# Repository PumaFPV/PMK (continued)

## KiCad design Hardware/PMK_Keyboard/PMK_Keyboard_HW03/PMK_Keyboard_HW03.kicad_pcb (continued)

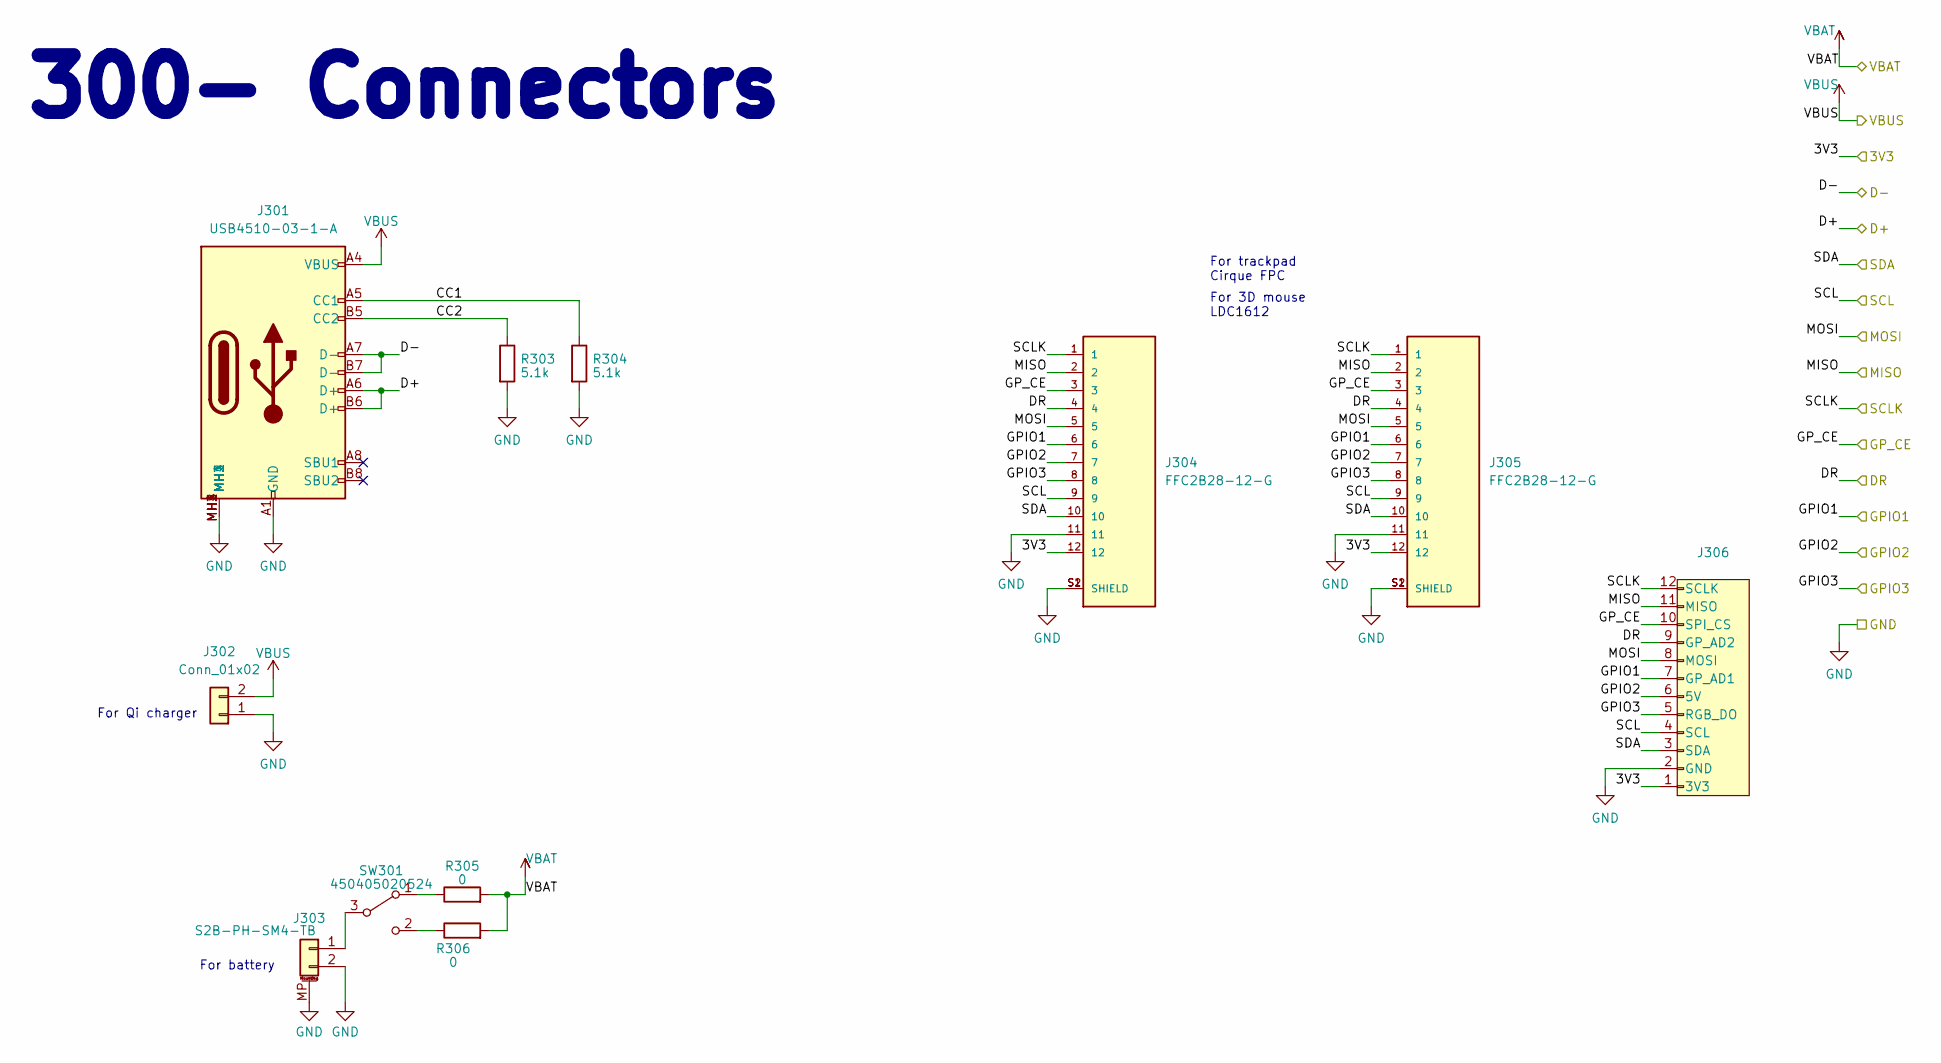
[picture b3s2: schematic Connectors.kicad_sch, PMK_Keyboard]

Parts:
J301: USB4510-03-1-A; USB4510031A; Mouser Part Number 640-USB4510031A
J302: Conn_01x02; PinHeader_1x02_P2.54mm_Vertical
J303: S2B-PH-SM4-TB; JST_PH_S2B-PH-SM4-TB_1x02-1MP_P2.00mm_Horizontal_DUALSIDE
J304, J305: FFC2B28-12-G; GCT_FFC2B28-12-G; PARTREV A; DigiKey_Part_Number 2073-FFC2B28-12-GTR-ND
J306: vik-keyboard-connector-horizontal
R303, R304: 5.1k; R_0402_1005Metric
R305, R306: 0; R_0402_1005Metric
SW301: 450405020524; 450405020524_DUALSIDE

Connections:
+3V3: J304.12, J305.12, J306.1 (3V3); also elsewhere on the board
/200- PSoM/D+: J301.A6 (D+), J301.B6 (D+); also elsewhere on the board
/200- PSoM/D-: J301.A7 (D-), J301.B7 (D-); also elsewhere on the board
/200- PSoM/DR: J304.4, J305.4, J306.9 (GP_AD2); also elsewhere on the board
/200- PSoM/GPIO1: J304.6, J305.6, J306.7 (GP_AD1); also elsewhere on the board
/200- PSoM/GPIO2: J304.7, J305.7, J306.6 (5V); also elsewhere on the board
/200- PSoM/GPIO3: J304.8, J305.8, J306.5 (RGB_DO); also elsewhere on the board
/200- PSoM/GP_CE: J304.3, J305.3, J306.10 (SPI_CS); also elsewhere on the board
/200- PSoM/SCL: J304.9, J305.9, J306.4 (SCL); also elsewhere on the board
/200- PSoM/SDA: J304.10, J305.10, J306.3 (SDA); also elsewhere on the board
/200- PSoM/SPI_CLK: J304.1, J305.1, J306.12 (SCLK); also elsewhere on the board
/200- PSoM/SPI_MISO: J304.2, J305.2, J306.11 (MISO); also elsewhere on the board
/200- PSoM/SPI_MOSI: J304.5, J305.5, J306.8 (MOSI); also elsewhere on the board
/300- Connectors/CC1: J301.A5 (CC1), R304.1
/300- Connectors/CC2: J301.B5 (CC2), R303.1
/VBAT: R305.2, R306.2; also elsewhere on the board
GND: J301.A1 (GND), J301.A12 (GND), J301.B1 (GND), J301.B12 (GND), J301.MH1, J301.MH2, J301.MH3, J301.MH4, J302.1, J303.2, J303.MP (MountPin), J304.11, J304.S1 (SHIELD), J304.S2 (SHIELD), J305.11, J305.S1 (SHIELD), J305.S2 (SHIELD), J306.2 (GND), R303.2, R304.2; also elsewhere on the board
unnamed: J303.1, SW301.3 (B)
unnamed: R305.1, SW301.1 (A)
unnamed: R306.1, SW301.2 (C)
VBUS: J301.A4 (VBUS), J301.A9 (VBUS), J301.B4 (VBUS), J301.B9 (VBUS), J302.2; also elsewhere on the board

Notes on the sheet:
300- Connectors
For battery
For trackpad Cirque FPC
For Qi charger
For 3D mouse LDC1612

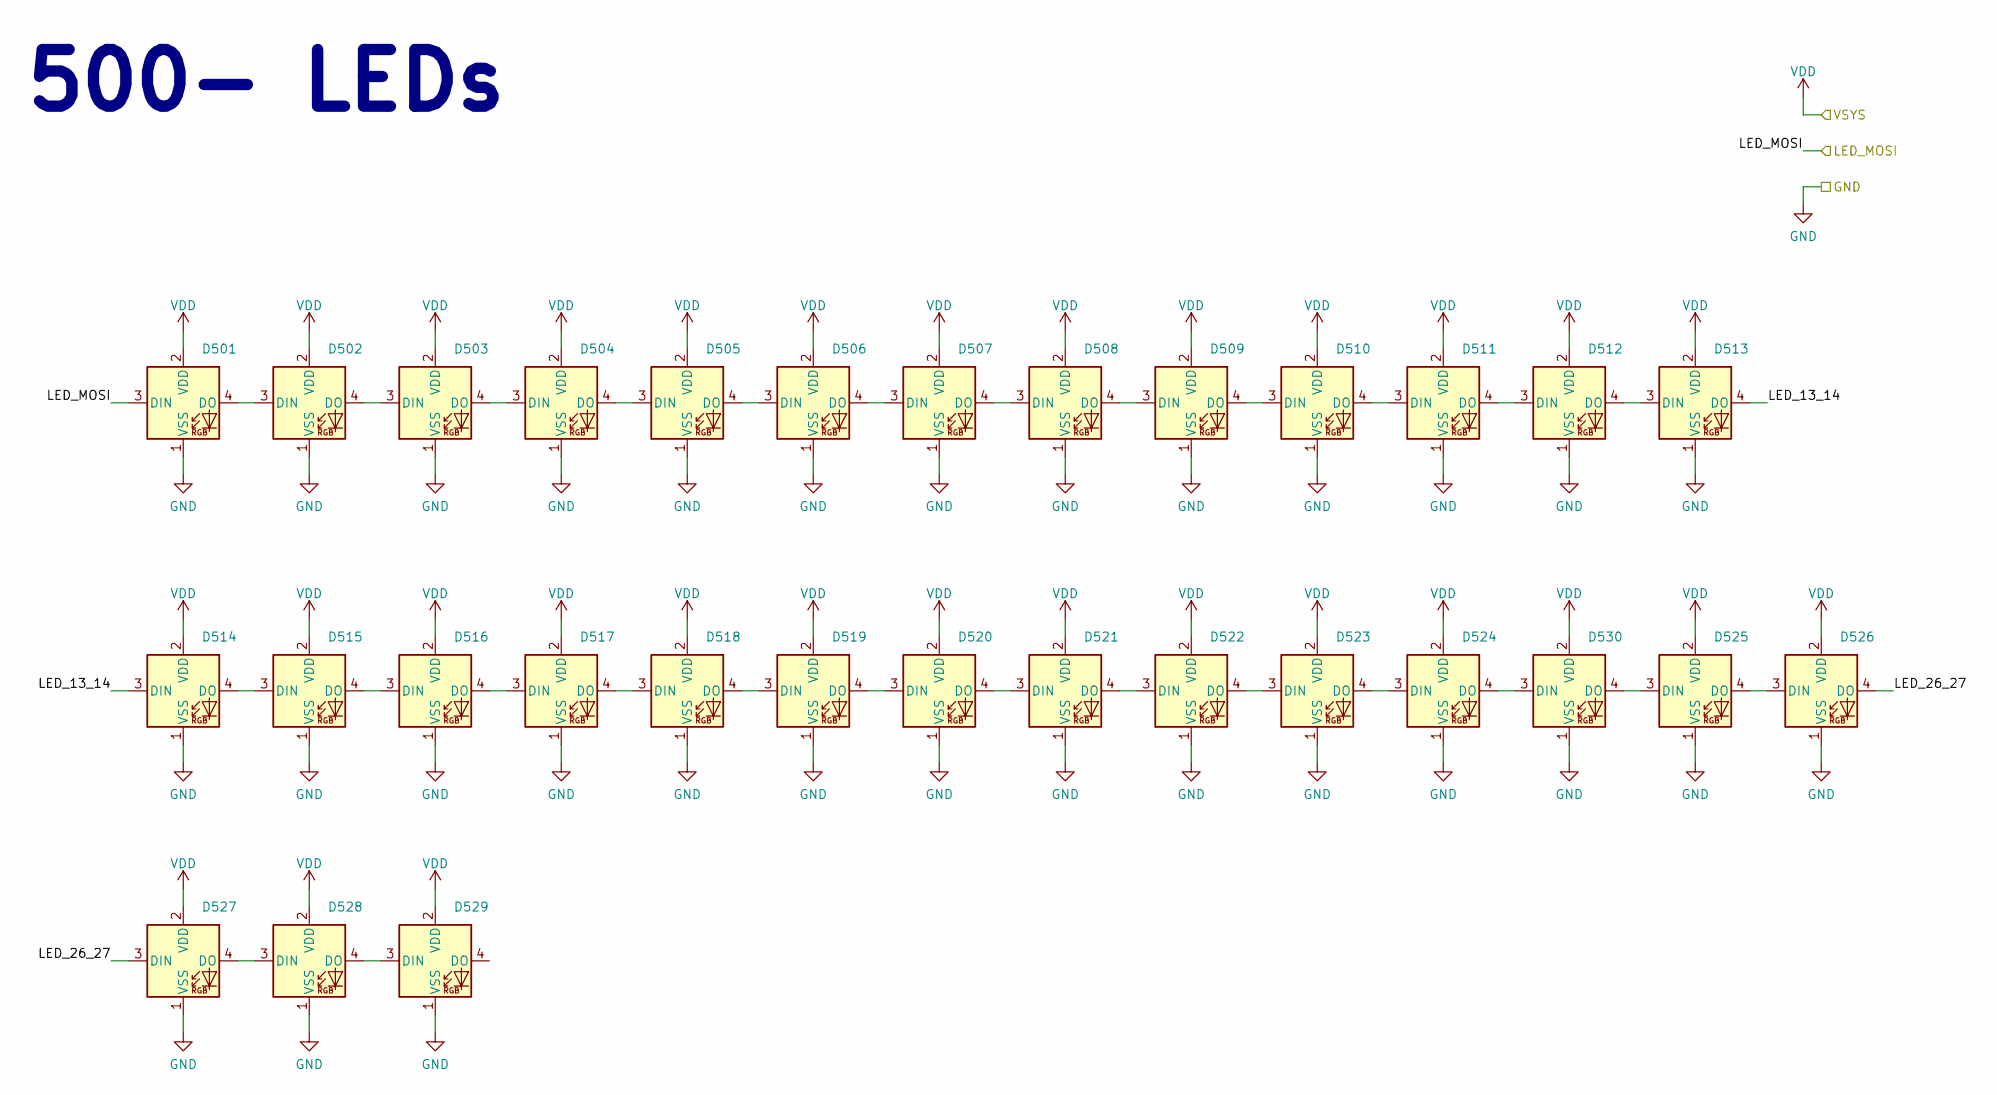
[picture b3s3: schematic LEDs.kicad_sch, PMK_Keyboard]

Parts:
D501, D502, D503, D504, D505, D506, D507, D508, D509, D510, D511, D512, D513, D514, D515, D516, D517, D518, D519, D520, D521, D522, D523, D524, D525, D526, D527, D528, D529, D530: YF923_2020_WS2812_LED; YF923_2020_WS2812_LED_DUALSIDE

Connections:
/200- PSoM/LED_MOSI: D501.3 (DIN); also elsewhere on the board
/500- LEDs/LED_13_14: D513.4 (DO), D514.3 (DIN)
/500- LEDs/LED_26_27: D526.4 (DO), D527.3 (DIN)
GND: D501.1 (VSS), D502.1 (VSS), D503.1 (VSS), D504.1 (VSS), D505.1 (VSS), D506.1 (VSS), D507.1 (VSS), D508.1 (VSS), D509.1 (VSS), D510.1 (VSS), D511.1 (VSS), D512.1 (VSS), D513.1 (VSS), D514.1 (VSS), D515.1 (VSS), D516.1 (VSS), D517.1 (VSS), D518.1 (VSS), D519.1 (VSS), D520.1 (VSS), D521.1 (VSS), D522.1 (VSS), D523.1 (VSS), D524.1 (VSS), D525.1 (VSS), D526.1 (VSS), D527.1 (VSS), D528.1 (VSS), D529.1 (VSS), D530.1 (VSS); also elsewhere on the board
unnamed: D501.4 (DO), D502.3 (DIN)
unnamed: D502.4 (DO), D503.3 (DIN)
unnamed: D503.4 (DO), D504.3 (DIN)
unnamed: D504.4 (DO), D505.3 (DIN)
unnamed: D505.4 (DO), D506.3 (DIN)
unnamed: D506.4 (DO), D507.3 (DIN)
unnamed: D507.4 (DO), D508.3 (DIN)
unnamed: D508.4 (DO), D509.3 (DIN)
unnamed: D509.4 (DO), D510.3 (DIN)
unnamed: D510.4 (DO), D511.3 (DIN)
unnamed: D511.4 (DO), D512.3 (DIN)
unnamed: D512.4 (DO), D513.3 (DIN)
unnamed: D514.4 (DO), D515.3 (DIN)
unnamed: D515.4 (DO), D516.3 (DIN)
unnamed: D516.4 (DO), D517.3 (DIN)
unnamed: D517.4 (DO), D518.3 (DIN)
unnamed: D518.4 (DO), D519.3 (DIN)
unnamed: D519.4 (DO), D520.3 (DIN)
unnamed: D520.4 (DO), D521.3 (DIN)
unnamed: D521.4 (DO), D522.3 (DIN)
unnamed: D522.4 (DO), D523.3 (DIN)
unnamed: D523.4 (DO), D524.3 (DIN)
unnamed: D524.4 (DO), D530.3 (DIN)
unnamed: D525.3 (DIN), D530.4 (DO)
unnamed: D525.4 (DO), D526.3 (DIN)
unnamed: D527.4 (DO), D528.3 (DIN)
unnamed: D528.4 (DO), D529.3 (DIN)
VDD: D501.2 (VDD), D502.2 (VDD), D503.2 (VDD), D504.2 (VDD), D505.2 (VDD), D506.2 (VDD), D507.2 (VDD), D508.2 (VDD), D509.2 (VDD), D510.2 (VDD), D511.2 (VDD), D512.2 (VDD), D513.2 (VDD), D514.2 (VDD), D515.2 (VDD), D516.2 (VDD), D517.2 (VDD), D518.2 (VDD), D519.2 (VDD), D520.2 (VDD), D521.2 (VDD), D522.2 (VDD), D523.2 (VDD), D524.2 (VDD), D525.2 (VDD), D526.2 (VDD), D527.2 (VDD), D528.2 (VDD), D529.2 (VDD), D530.2 (VDD); also elsewhere on the board

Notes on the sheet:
500- LEDs

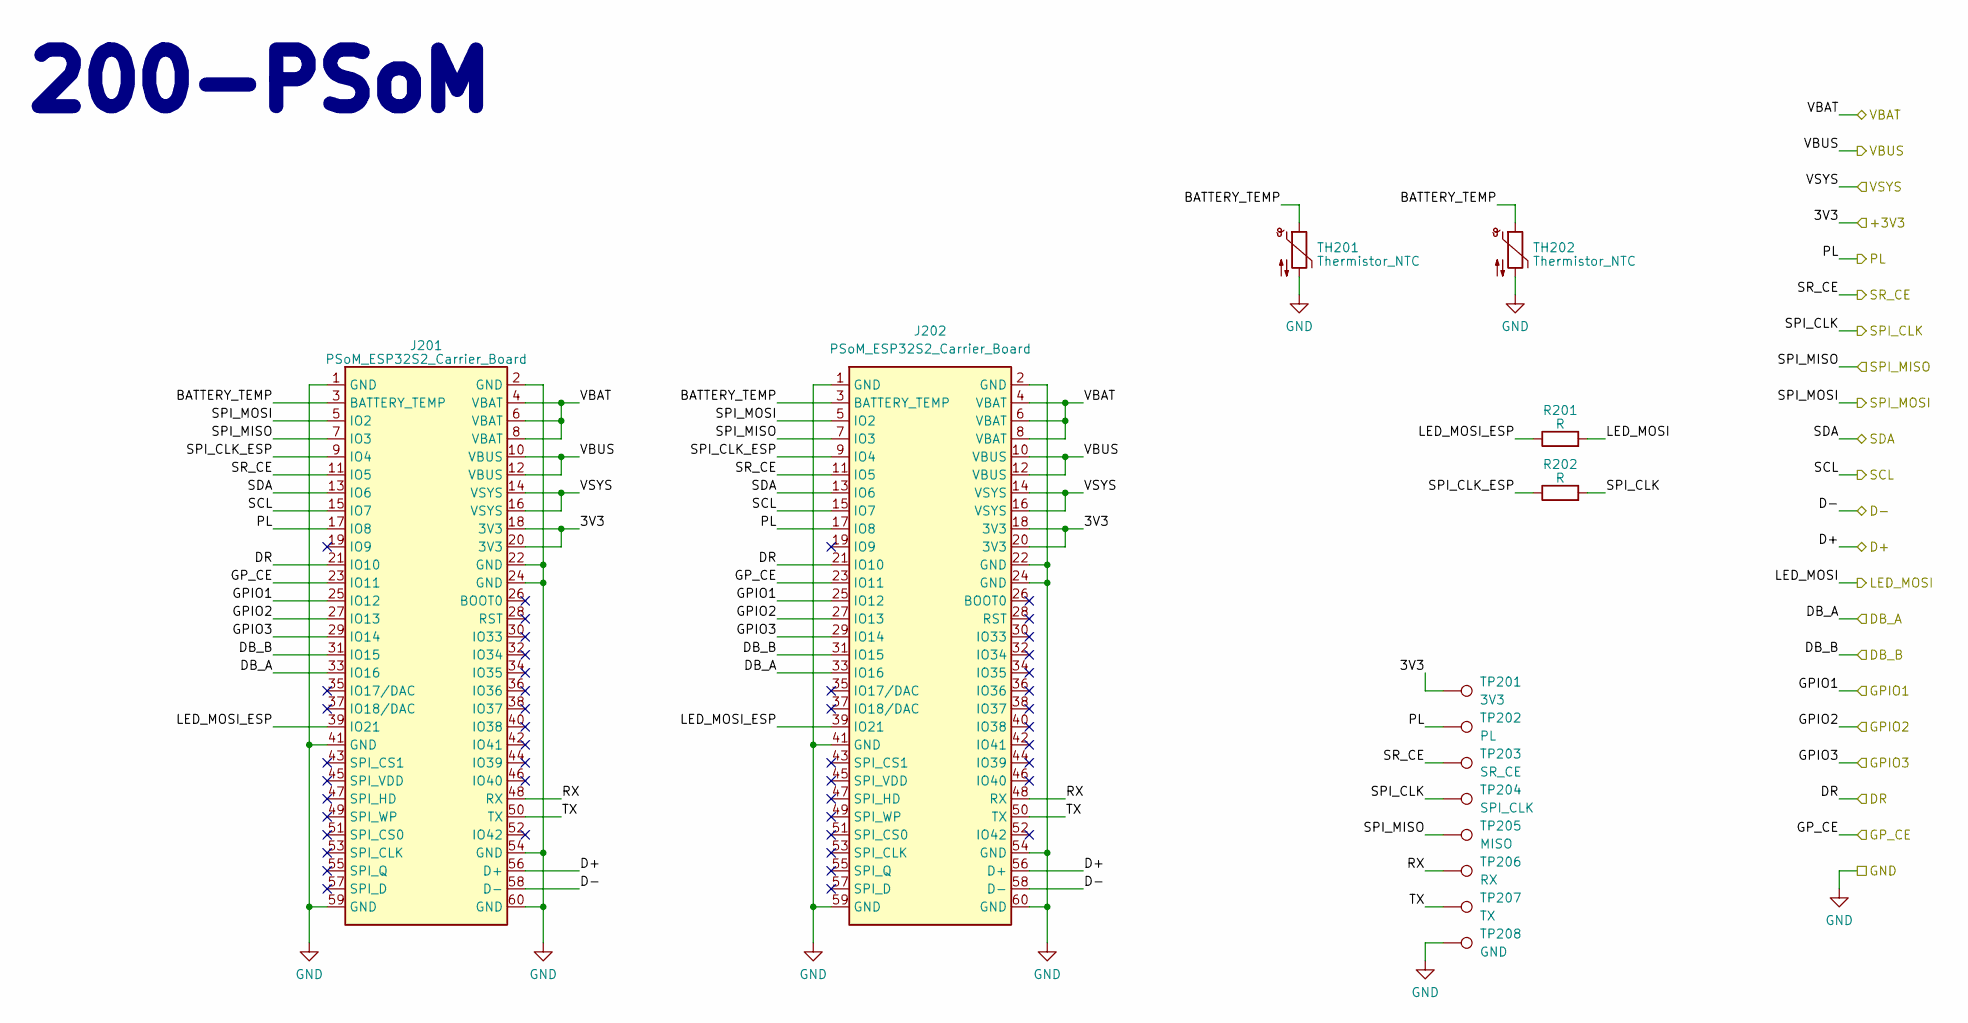
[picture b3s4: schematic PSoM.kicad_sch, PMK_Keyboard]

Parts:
J201, J202: PSoM_ESP32S2_Carrier_Board; PSoM_ESP32S2_00
R201, R202: R; R_0402_1005Metric
TH201, TH202: Thermistor_NTC; R_0402_1005Metric
TP201: 3V3; TestPoint_Pad_D1.5mm
TP202: PL; TestPoint_Pad_D1.5mm
TP203: SR_CE; TestPoint_Pad_D1.5mm
TP204: SPI_CLK; TestPoint_Pad_D1.5mm
TP205: MISO; TestPoint_Pad_D1.5mm
TP206: RX; TestPoint_Pad_D1.5mm
TP207: TX; TestPoint_Pad_D1.5mm
TP208: GND; TestPoint_Pad_D1.5mm

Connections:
+3V3: J201.18 (3V3), J201.20 (3V3), J202.18 (3V3), J202.20 (3V3), TP201.1; also elsewhere on the board
/200- PSoM/BATTERY_TEMP: J201.3 (BATTERY_TEMP), J202.3 (BATTERY_TEMP), TH201.1, TH202.1
/200- PSoM/D+: J201.56 (D+), J202.56 (D+); also elsewhere on the board
/200- PSoM/D-: J201.58 (D-), J202.58 (D-); also elsewhere on the board
/200- PSoM/DB_A: J201.33 (IO16), J202.33 (IO16); also elsewhere on the board
/200- PSoM/DB_B: J201.31 (IO15), J202.31 (IO15); also elsewhere on the board
/200- PSoM/DR: J201.21 (IO10), J202.21 (IO10); also elsewhere on the board
/200- PSoM/GPIO1: J201.25 (IO12), J202.25 (IO12); also elsewhere on the board
/200- PSoM/GPIO2: J201.27 (IO13), J202.27 (IO13); also elsewhere on the board
/200- PSoM/GPIO3: J201.29 (IO14), J202.29 (IO14); also elsewhere on the board
/200- PSoM/GP_CE: J201.23 (IO11), J202.23 (IO11); also elsewhere on the board
/200- PSoM/LED_MOSI: R201.2; also elsewhere on the board
/200- PSoM/LED_MOSI_ESP: J201.39 (IO21), J202.39 (IO21), R201.1
/200- PSoM/PL: J201.17 (IO8), J202.17 (IO8), TP202.1; also elsewhere on the board
/200- PSoM/RX: J201.48 (RX), J202.48 (RX), TP206.1
/200- PSoM/SCL: J201.15 (IO7), J202.15 (IO7); also elsewhere on the board
/200- PSoM/SDA: J201.13 (IO6), J202.13 (IO6); also elsewhere on the board
/200- PSoM/SPI_CLK: R202.2, TP204.1; also elsewhere on the board
/200- PSoM/SPI_CLK_ESP: J201.9 (IO4), J202.9 (IO4), R202.1
/200- PSoM/SPI_MISO: J201.7 (IO3), J202.7 (IO3), TP205.1; also elsewhere on the board
/200- PSoM/SPI_MOSI: J201.5 (IO2), J202.5 (IO2); also elsewhere on the board
/200- PSoM/SR_CE: J201.11 (IO5), J202.11 (IO5), TP203.1; also elsewhere on the board
/200- PSoM/TX: J201.50 (TX), J202.50 (TX), TP207.1
/VBAT: J201.4 (VBAT), J201.6 (VBAT), J201.8 (VBAT), J202.4 (VBAT), J202.6 (VBAT), J202.8 (VBAT); also elsewhere on the board
GND: J201.1 (GND), J201.2 (GND), J201.22 (GND), J201.24 (GND), J201.41 (GND), J201.54 (GND), J201.59 (GND), J201.60 (GND), J202.1 (GND), J202.2 (GND), J202.22 (GND), J202.24 (GND), J202.41 (GND), J202.54 (GND), J202.59 (GND), J202.60 (GND), TH201.2, TH202.2, TP208.1; also elsewhere on the board
VBUS: J201.10 (VBUS), J201.12 (VBUS), J202.10 (VBUS), J202.12 (VBUS); also elsewhere on the board
VDD: J201.14 (VSYS), J201.16 (VSYS), J202.14 (VSYS), J202.16 (VSYS); also elsewhere on the board

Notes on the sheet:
200-PSoM

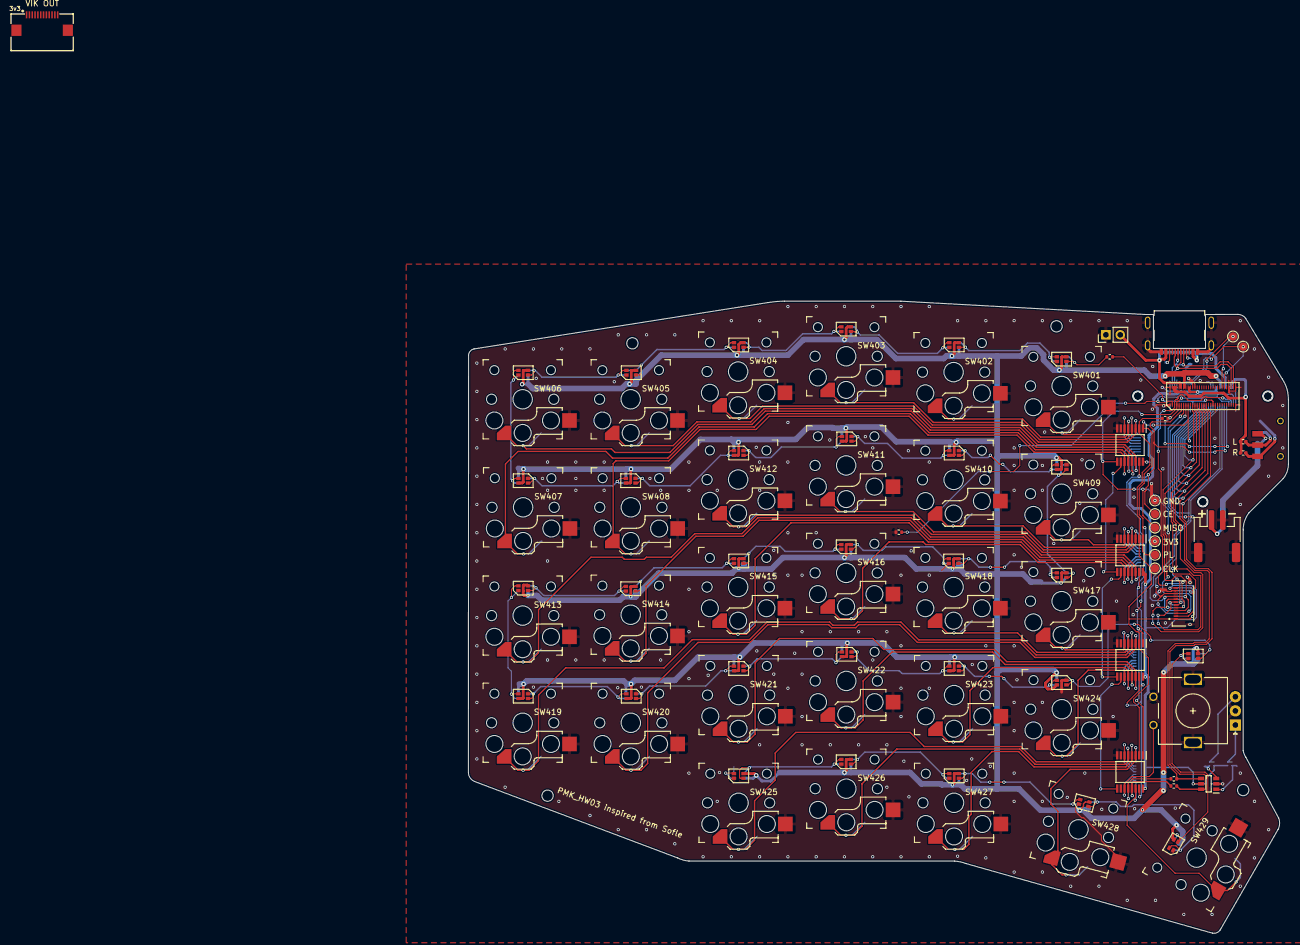
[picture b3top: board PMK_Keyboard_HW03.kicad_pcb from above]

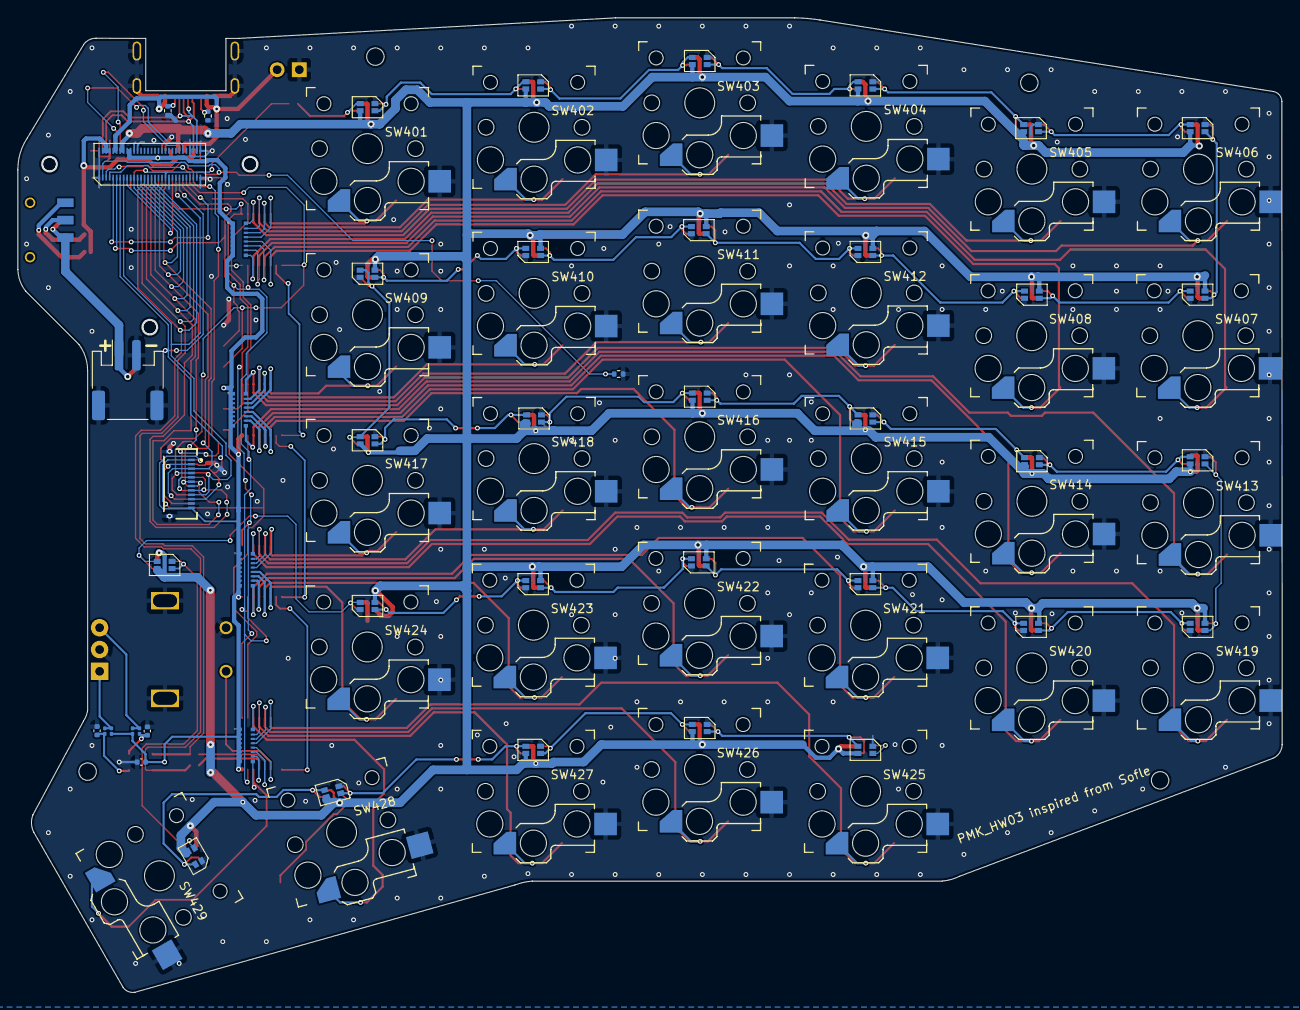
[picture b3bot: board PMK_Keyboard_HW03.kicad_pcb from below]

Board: 2 copper layers, 145.0 x 111.8 mm, 103 parts (17 on the bottom side), 100 nets.

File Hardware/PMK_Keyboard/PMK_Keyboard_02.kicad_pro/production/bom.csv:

Designator,Footprint,Quantity,Value,LCSC Part #
"C401, C402",0402,2,10n,
C403,0402,1,100n,
"D501, D502, D503, D504, D505, D506, D507, D508, D509, D510, D511, D512, D513, D514, D515, D516, D517, D518, D519, D520, D521, D522, D523, D524, D525, D526, D527, D528, D529, D530",YF923_2020_WS2812_LED_DUALSIDE,30,YF923_2020_WS2812_LED,
"J201, J202",PSoM_ESP32S2_00,2,PSoM_ESP32S2_Carrier_Board,
J301,USB4510031A,1,USB4510-03-1-A,
J302,PinHeader_1x02_P2.54mm_Vertical,1,Conn_01x02,
J303,JST_PH_S2B-PH-SM4-TB_1x02-1MP_P2.00mm_Horizontal_DUALSIDE,1,S2B-PH-SM4-TB,
"J304, J305",GCT_FFC2B28-12-G,2,FFC2B28-12-G,
"R201, R202",0402,2,R,
"R303, R304",0402,2,5.1k,
"R305, R306",0402,2,0,
"R401, R402, R403, R404",0201,4,10k,
"RN401, RN402, RN403, RN404",EXB2HV_1,4,EXB-2HV103JV,
SW301,450405020524_DUALSIDE,1,450405020524,
"SW401, SW402, SW403, SW404, SW405, SW406, SW407, SW408, SW409, SW410, SW411, SW412, SW413, SW414, SW415, SW416, SW417, SW418, SW419, SW420, SW421, SW422, SW423, SW424, SW425, SW426, SW427, SW428, SW429",Kailh_socket_PG1350_reversible_V1V2,29,SW_Push,
SW430,RIC11-22S10D5S-TH,1,RIC11-22S10D5S-TH,
"TH201, TH202",0402,2,Thermistor_NTC,
TP201,TestPoint_Pad_D1.5mm,1,3V3,
TP202,TestPoint_Pad_D1.5mm,1,PL,
TP203,TestPoint_Pad_D1.5mm,1,SR_CE,
TP204,TestPoint_Pad_D1.5mm,1,SPI_CLK,
TP205,TestPoint_Pad_D1.5mm,1,MISO,
TP206,TestPoint_Pad_D1.5mm,1,RX,
TP207,TestPoint_Pad_D1.5mm,1,TX,
TP208,TestPoint_Pad_D1.5mm,1,GND,
"U401, U402, U403, U404",SOP65P640X120-16N,4,SN74HC165PWR,
U405,SOP95P280X145-6N,1,SN74LVC2G04DBVRG4,

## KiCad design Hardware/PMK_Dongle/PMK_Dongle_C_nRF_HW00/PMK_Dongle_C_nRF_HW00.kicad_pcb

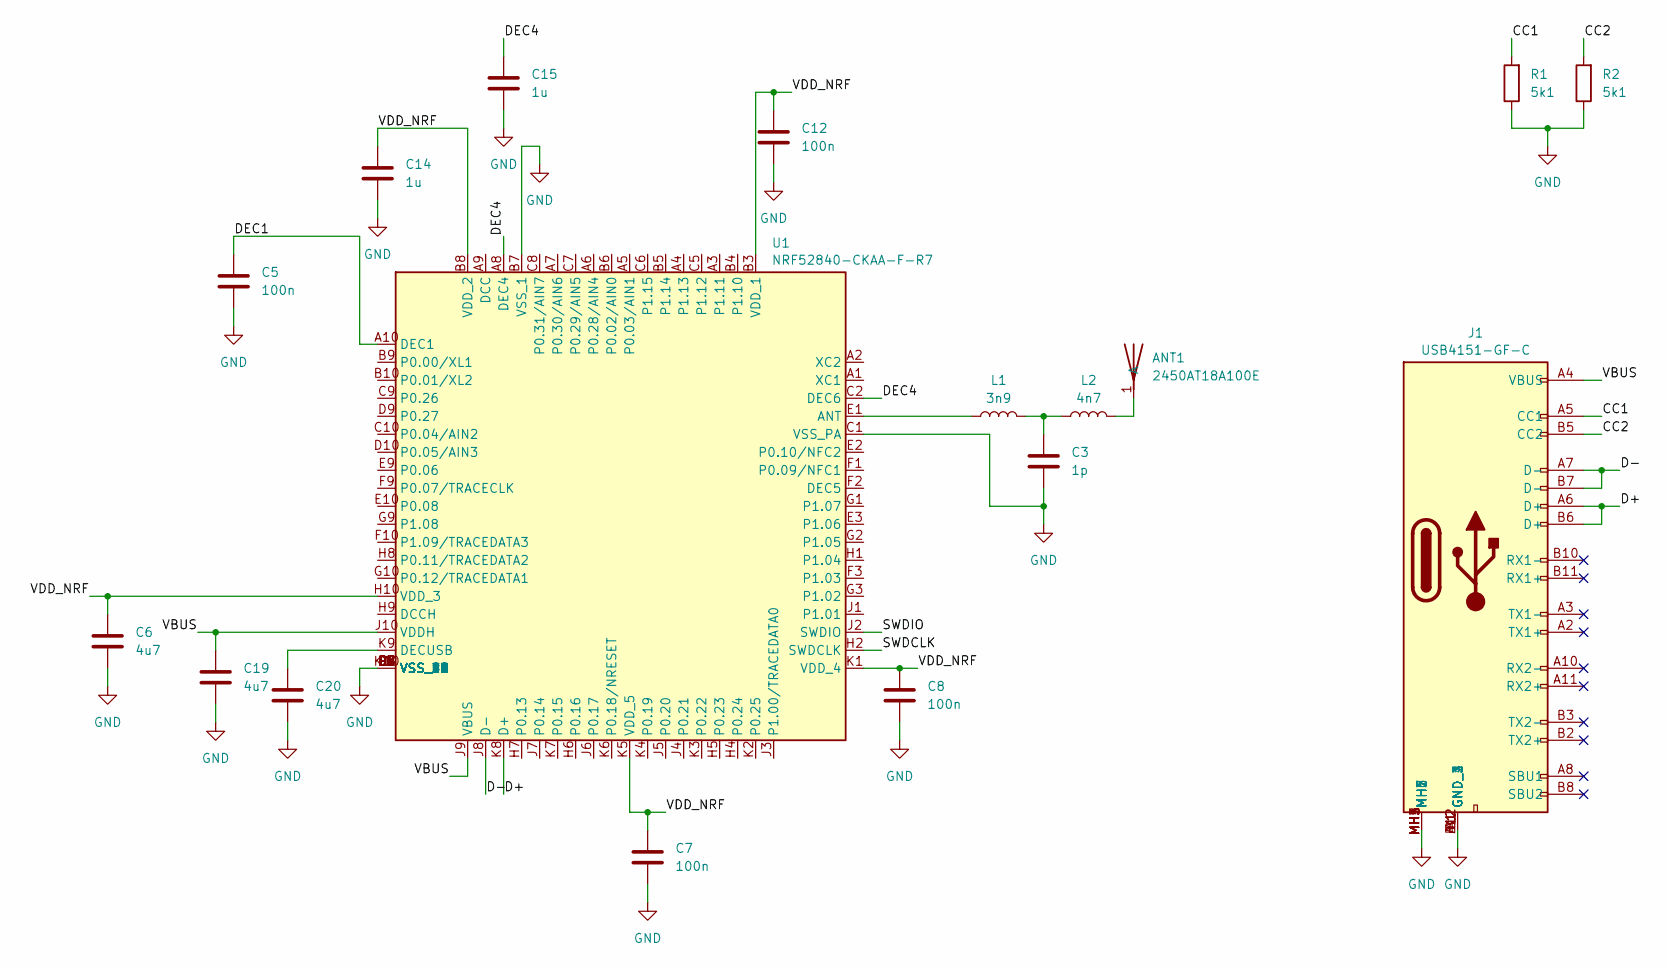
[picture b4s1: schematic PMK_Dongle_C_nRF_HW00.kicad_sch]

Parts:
ANT1: 2450AT18A100E; ANTC3216X140N; Mouser Part Number 609-2450AT18A100E
C3: 1p; C_0201_0603Metric
C5, C7, C8, C12: 100n; C_0201_0603Metric
C6, C19, C20: 4u7; C_0603_1608Metric
C14, C15: 1u; C_0402_1005Metric
J1: USB4151-GF-C; USB4151GFC; Mouser Part Number 640-USB4151-GF-C
L1: 3n9; L_0201_0603Metric
L2: 4n7; L_0201_0603Metric
R1, R2: 5k1; R_0201_0603Metric
U1: NRF52840-CKAA-F-R7; Mouser Part Number 949-NRF52840CKAAF-R7

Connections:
/CC1: J1.A5 (CC1), R1.2
/CC2: J1.B5 (CC2), R2.2
/D+: J1.A6 (D+), J1.B6 (D+), U1.K8 (D+)
/D-: J1.A7 (D-), J1.B7 (D-), U1.J8 (D-)
/DEC1: C5.1, U1.A10 (DEC1)
/DEC4: C15.1, U1.A8 (DEC4), U1.C2 (DEC6)
/SWDCLK: U1.H2 (SWDCLK)
/SWDIO: U1.J2 (SWDIO)
/VBUS: C19.1, J1.A4 (VBUS), J1.A9 (VBUS), J1.B4 (VBUS), J1.B9 (VBUS), U1.J9 (VBUS), U1.J10 (VDDH)
/VDD_NRF: C6.1, C7.1, C8.1, C12.1, C14.1, U1.B3 (VDD_1), U1.B8 (VDD_2), U1.H10 (VDD_3), U1.K1 (VDD_4), U1.K5 (VDD_5)
GND: C3.2, C5.2, C6.2, C7.2, C8.2, C12.2, C14.2, C15.2, C19.2, C20.2, J1.A1 (GND_1), J1.A12 (GND_2), J1.B1 (GND_3), J1.B12 (GND_4), J1.MH1, J1.MH2 (MH7), J1.MH3 (MH2), J1.MH4 (MH6), J1.MH5, R1.1, R2.1, U1.B7 (VSS_1), U1.C1 (VSS_PA), U1.C4 (VSS_2), U1.D3 (VSS_3), U1.D4 (VSS_4), U1.D5 (VSS_5), U1.D6 (VSS_6), U1.D7 (VSS_7), U1.D8 (VSS_8), U1.E4 (VSS_9), U1.E5 (VSS_10), U1.E6 (VSS_11), U1.E7 (VSS_12), U1.E8 (VSS_13), U1.F4 (VSS_14), U1.F5 (VSS_15), U1.F6 (VSS_16), U1.F7 (VSS_17), U1.F8 (VSS_18), U1.G4 (VSS_19), U1.G5 (VSS_20), U1.G6 (VSS_21), U1.G7 (VSS_22), U1.G8 (VSS_23), U1.K10 (VSS_24)
unnamed: ANT1.1 (A), L2.2
unnamed: C3.1, L1.2, L2.1
unnamed: L1.1, U1.E1 (ANT)
unnamed: C20.1, U1.K9 (DECUSB)

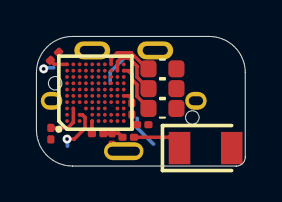
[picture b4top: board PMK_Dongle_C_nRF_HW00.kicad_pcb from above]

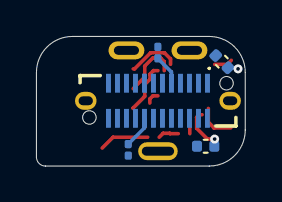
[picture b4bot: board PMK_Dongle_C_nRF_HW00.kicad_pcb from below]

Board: 6 copper layers, 11.6 x 7.2 mm, 17 parts (5 on the bottom side), 13 nets.

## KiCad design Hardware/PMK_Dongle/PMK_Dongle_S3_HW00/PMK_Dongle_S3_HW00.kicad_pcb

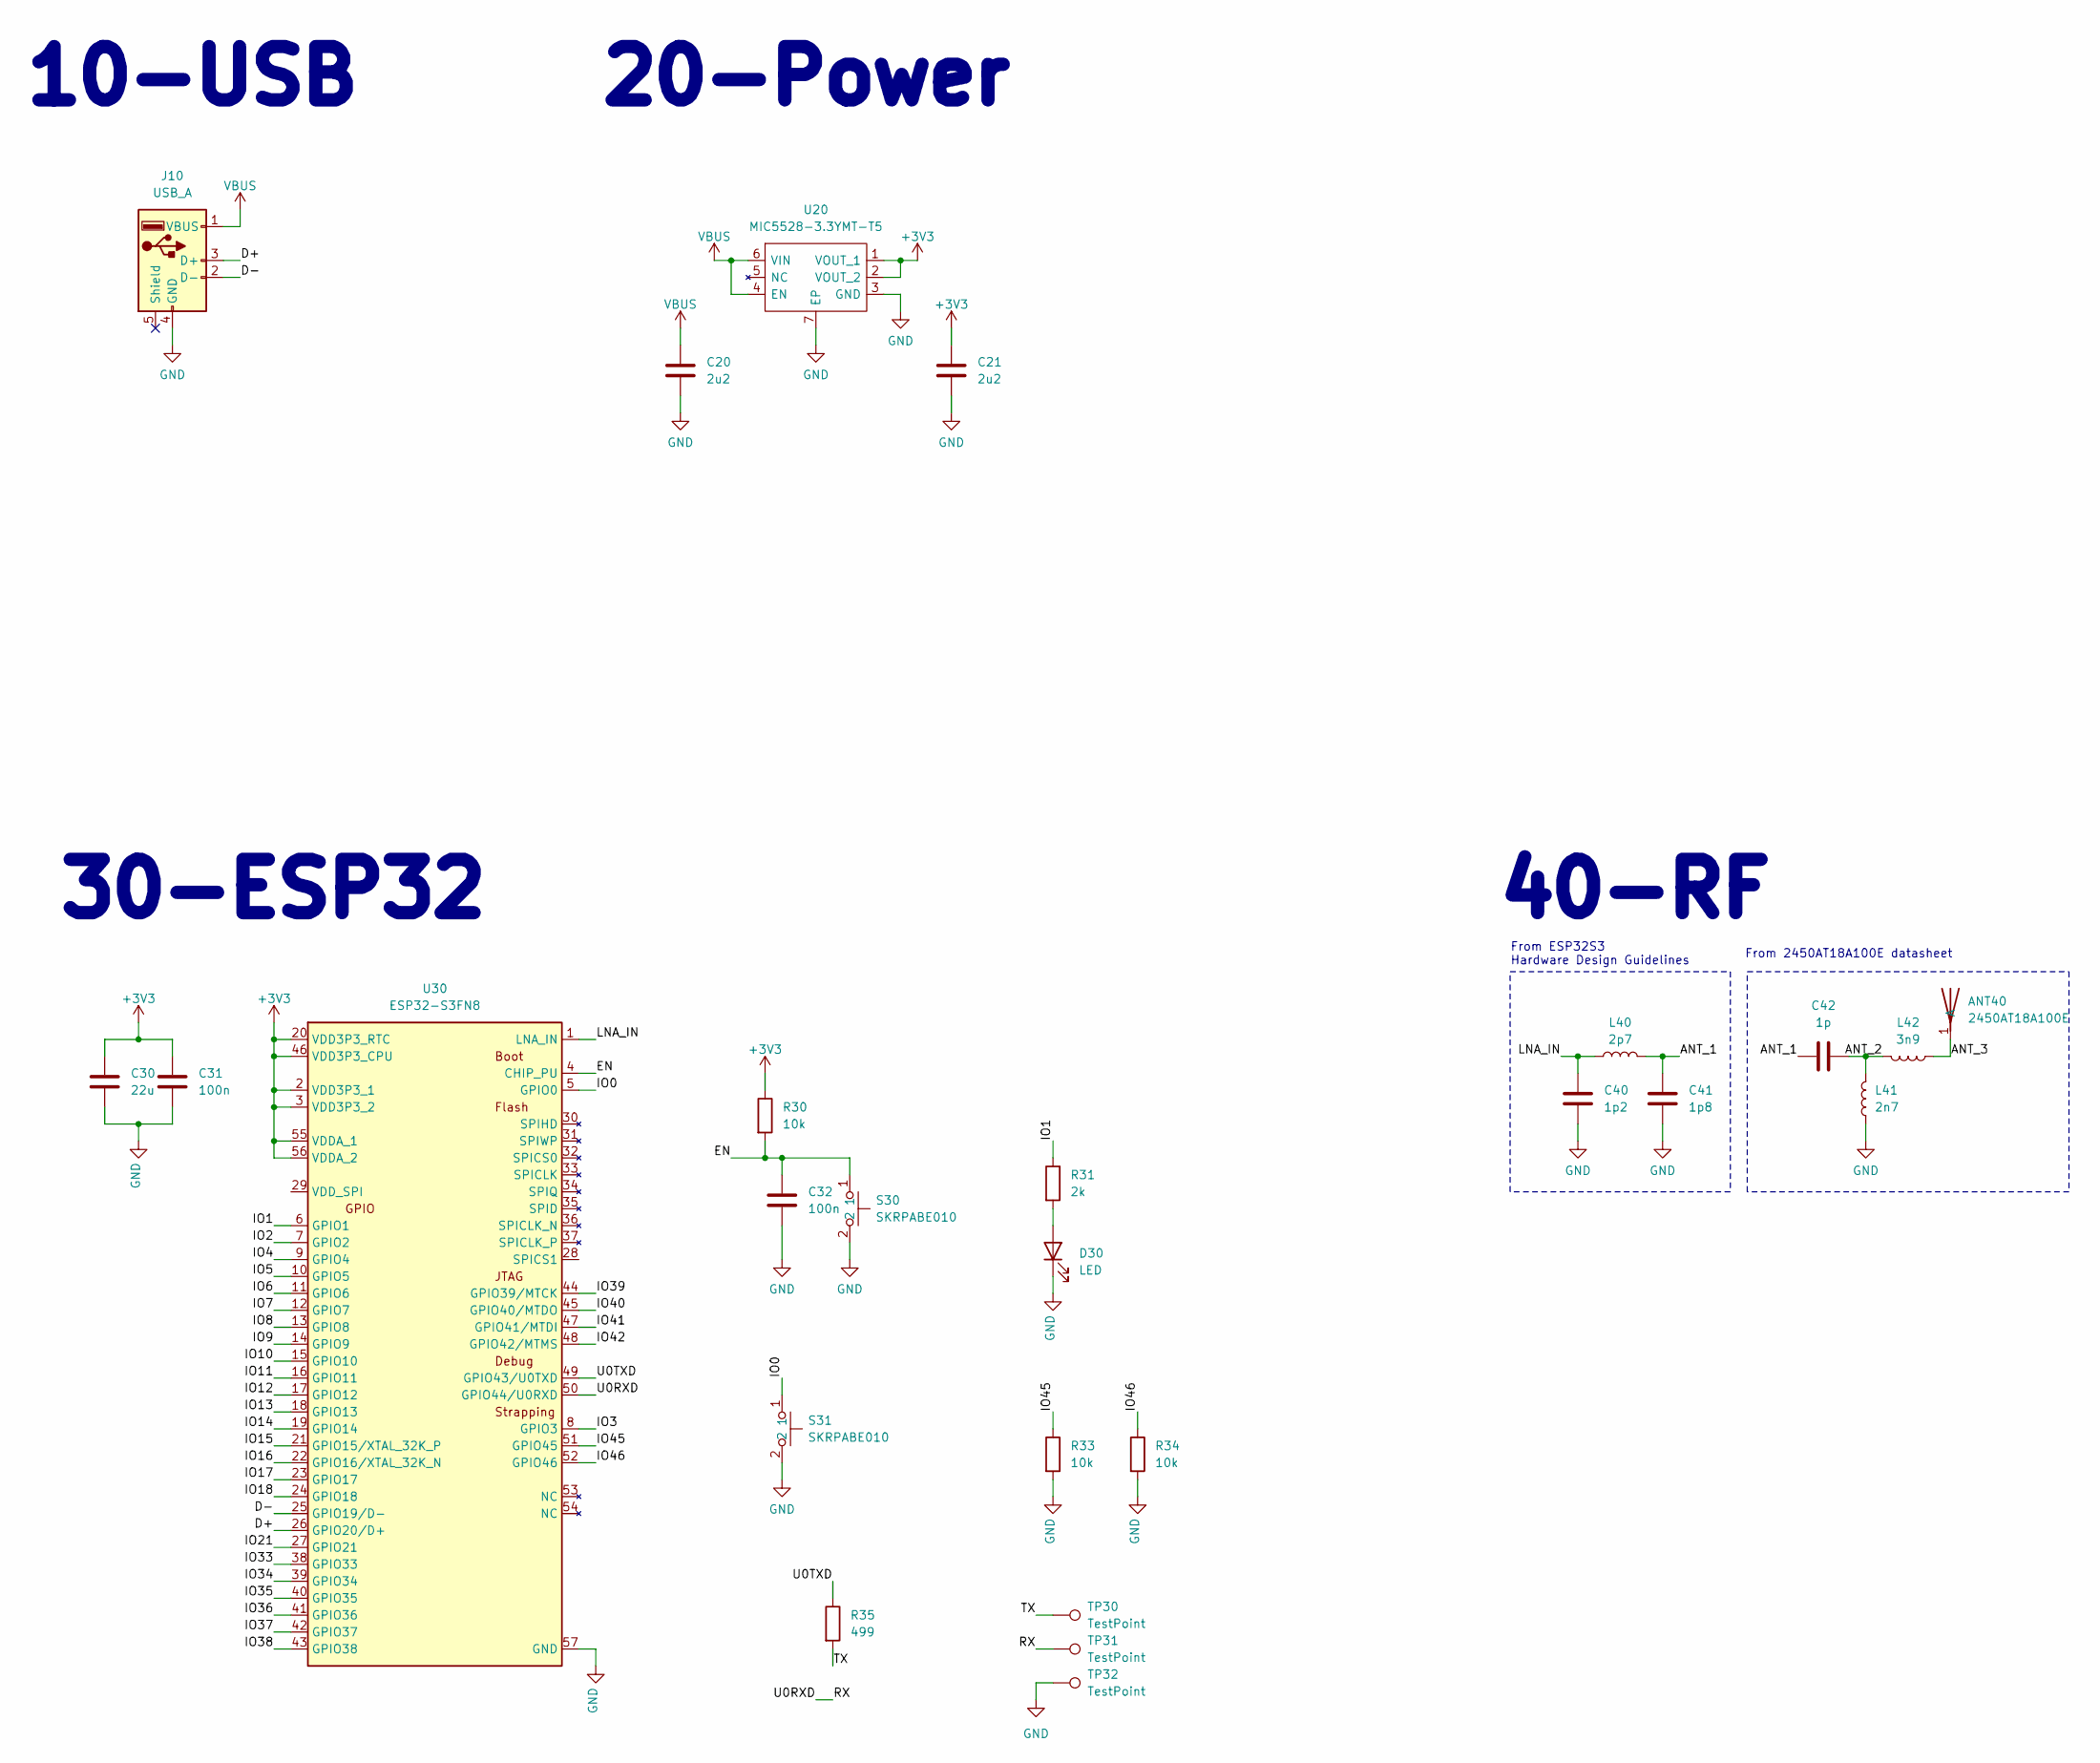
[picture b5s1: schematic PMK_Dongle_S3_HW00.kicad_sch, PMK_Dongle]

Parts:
ANT40: 2450AT18A100E; ANTC3216X140N; Mouser Part Number 609-2450AT18A100E
C20, C21: 2u2; C_0603_1608Metric
C30: 22u; C_0603_1608Metric
C31: 100n; C_0201_0603Metric
C32: 100n; C_0402_1005Metric
C40: 1p2; C_0201_0603Metric
C41: 1p8; C_0201_0603Metric
C42: 1p; C_0402_1005Metric
D30: LED; LED_0402_1005Metric
J10: USB_A; USB_PCB
L40: 2p7; L_0201_0603Metric
L41: 2n7; L_0402_1005Metric
L42: 3n9; L_0402_1005Metric
R30, R33, R34: 10k; R_0201_0603Metric
R31: 2k; R_0402_1005Metric
R35: 499; R_0402_1005Metric
S30, S31: SKRPABE010; B3U-1000P; Mouser Part Number 688-SKRPAB
TP30, TP31, TP32: TestPoint; TestPoint_0.8mm
U20: MIC5528-3.3YMT-T5; SON40P120X120X60-7N-D; Mouser Part Number 998-MIC5528-3.3YMTT5
U30: ESP32-S3FN8; ESP32-S3-PICO-1-N8R2; Mouser Part Number 356-ESP32-S3FN8

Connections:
+3V3: C21.1, C30.1, C31.1, R30.1, U20.1 (VOUT_1), U20.2 (VOUT_2), U30.2 (VDD3P3_1), U30.3 (VDD3P3_2), U30.20 (VDD3P3_RTC), U30.46 (VDD3P3_CPU), U30.55 (VDDA_1), U30.56 (VDDA_2)
/ANT_1: C41.1, C42.2, L40.1
/ANT_2: C42.1, L41.1, L42.1
/ANT_3: ANT40.1 (A), L42.2
/D+: J10.3 (D+), U30.26 (GPIO20/D+)
/D-: J10.2 (D-), U30.25 (GPIO19/D-)
/EN: C32.1, R30.2, S30.1, U30.4 (CHIP_PU)
/IO0: S31.1, U30.5 (GPIO0)
/IO1: R31.1, U30.6 (GPIO1)
/IO2: U30.7 (GPIO2)
/IO3: U30.8 (GPIO3)
/IO4: U30.9 (GPIO4)
/IO5: U30.10 (GPIO5)
/IO6: U30.11 (GPIO6)
/IO7: U30.12 (GPIO7)
/IO8: U30.13 (GPIO8)
/IO9: U30.14 (GPIO9)
/IO10: U30.15 (GPIO10)
/IO11: U30.16 (GPIO11)
/IO12: U30.17 (GPIO12)
/IO13: U30.18 (GPIO13)
/IO14: U30.19 (GPIO14)
/IO15: U30.21 (GPIO15/XTAL_32K_P)
/IO16: U30.22 (GPIO16/XTAL_32K_N)
/IO17: U30.23 (GPIO17)
/IO18: U30.24 (GPIO18)
/IO21: U30.27 (GPIO21)
/IO33: U30.38 (GPIO33)
/IO34: U30.39 (GPIO34)
/IO35: U30.40 (GPIO35)
/IO36: U30.41 (GPIO36)
/IO37: U30.42 (GPIO37)
/IO38: U30.43 (GPIO38)
/IO39: U30.44 (GPIO39/MTCK)
/IO40: U30.45 (GPIO40/MTDO)
/IO41: U30.47 (GPIO41/MTDI)
/IO42: U30.48 (GPIO42/MTMS)
/IO45: R33.1, U30.51 (GPIO45)
/IO46: R34.1, U30.52 (GPIO46)
/LNA_IN: C40.1, L40.2, U30.1 (LNA_IN)
/RX: TP31.1, U30.50 (GPIO44/U0RXD)
/TX: R35.2, TP30.1
/U0TXD: R35.1, U30.49 (GPIO43/U0TXD)
GND: C20.2, C21.2, C30.2, C31.2, C32.2, C40.2, C41.2, D30.1 (K), J10.4 (GND), L41.2, R33.2, R34.2, S30.2, S31.2, TP32.1, U20.3 (GND), U20.7 (EP), U30.57 (GND)
unnamed: D30.2 (A), R31.2
VBUS: C20.1, J10.1 (VBUS), U20.4 (EN), U20.6 (VIN)

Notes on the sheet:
From 2450AT18A100E datasheet
40-RF
10-USB
30-ESP32
From ESP32S3 Hardware Design Guidelines
20-Power

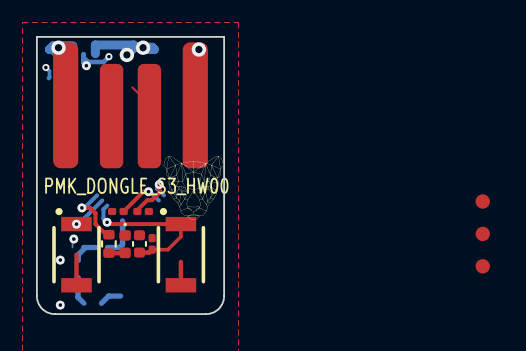
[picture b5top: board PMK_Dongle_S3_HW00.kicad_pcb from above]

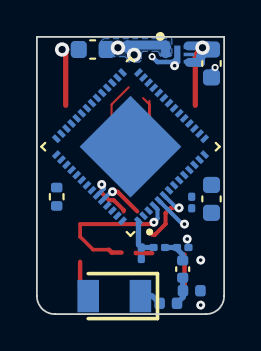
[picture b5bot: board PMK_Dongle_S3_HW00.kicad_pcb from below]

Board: 4 copper layers, 10.4 x 15.4 mm, 26 parts (14 on the bottom side), 18 nets.
